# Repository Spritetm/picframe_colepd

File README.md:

### What is this?

This is the firmware, PCB artwork, schematics and case design for a WiFi-enabled color picture frame.

### Contents

- case - OpenSCAD program to build the case. Change the 'render' variable to render the various parts.
- www - PHP and C program running on the server that is used to upload/fetch the pictures.
- firmware - ESP32C3 firmware. Make sure to run menuconfig to point this at your server.
- pcb - Schematics and PCB artwork, in Kicad format.

### More information

[Article on Spritesmods](https://spritesmods.com/?art=wifipicframe)

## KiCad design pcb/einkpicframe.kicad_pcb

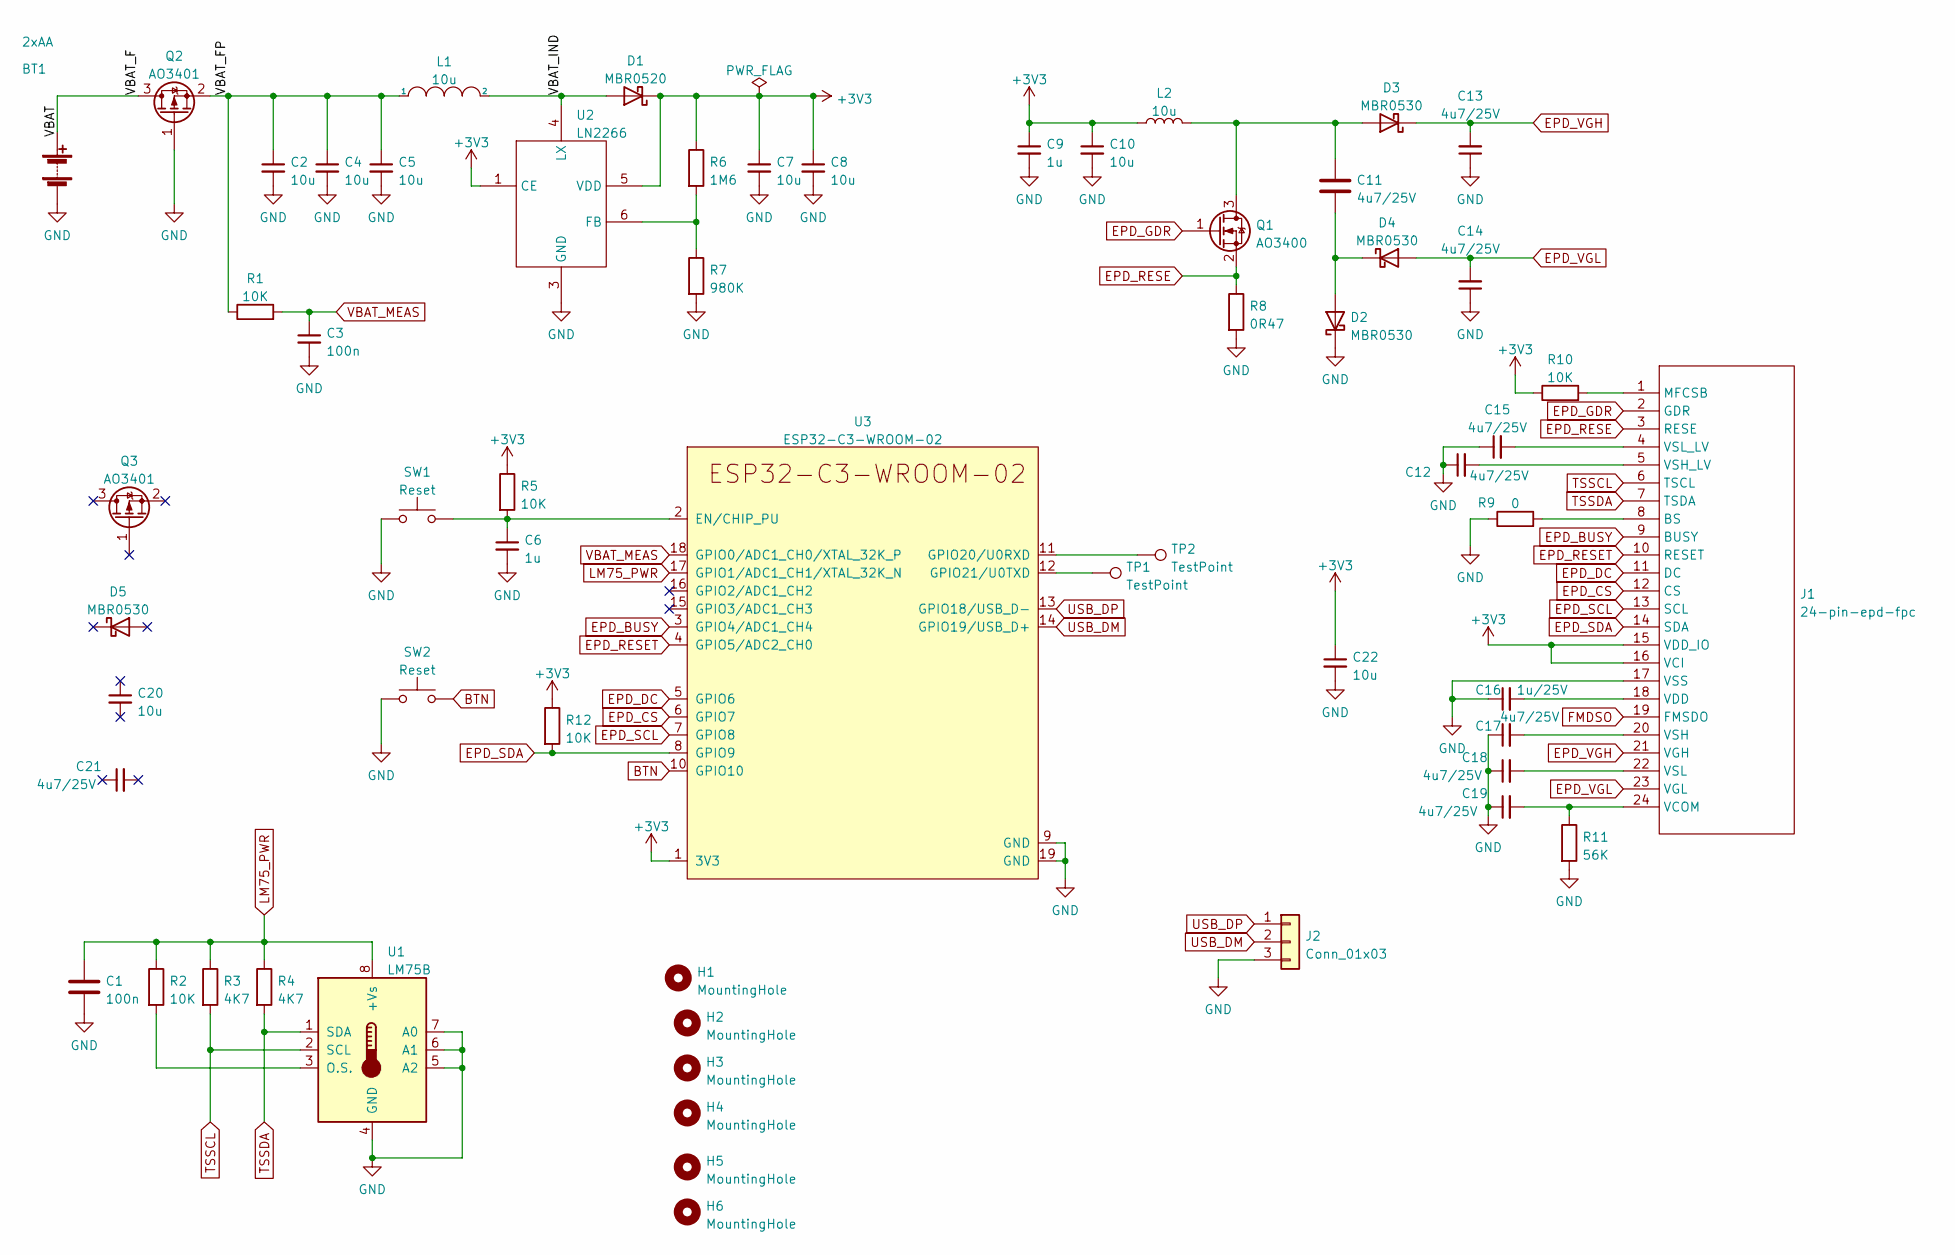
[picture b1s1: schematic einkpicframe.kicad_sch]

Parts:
BT1: 2xAA; 2xaa_pcb_conn
C1, C3: 100n; C_0603_1608Metric
C2, C4, C5, C7, C8, C10, C20, C22: 10u; C_0805_2012Metric
C6, C9: 1u; C_0603_1608Metric
C11, C12, C13, C14, C15, C17, C18, C19, C21: 4u7/25V; C_0603_1608Metric
C16: 1u/25V; C_0603_1608Metric
D1: MBR0520; D_SOD-123
D2, D3, D4, D5: MBR0530; D_SOD-123
H1, H2, H3, H4, H5, H6: MountingHole; MountingHole_3.2mm_M3_ISO14580
J1: 24-pin-epd-fpc; Hirose_FH12-24S-0.5SH_1x24-1MP_P0.50mm_Horizontal_reverse
J2: Conn_01x03; PinHeader_1x03_P2.54mm_Horizontal
L1, L2: 10u; IND_WHC0630
Q1: AO3400; SOT-23
Q2, Q3: AO3401; SOT-23W_Handsoldering
R1, R2, R5, R10, R12: 10K; R_0603_1608Metric
R3, R4: 4K7; R_0603_1608Metric
R6: 1M6; R_0603_1608Metric
R7: 980K; R_0603_1608Metric
R8: 0R47; R_0603_1608Metric
R9: 0; R_0603_1608Metric
R11: 56K; R_0603_1608Metric
SW1, SW2: Reset; SW_SPST_B3S-1000
TP1, TP2: TestPoint; TestPoint_Pad_1.5x1.5mm
U1: LM75B; TSSOP-8_3x3mm_P0.65mm
U2: LN2266; SOT-23-6
U3: ESP32-C3-WROOM-02

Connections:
+3V3: C7.1, C8.1, C9.1, C10.1, C22.1, D1.1 (K), J1.15 (VDD_IO), J1.16 (VCI), L2.1, R5.1, R6.1, R10.1, R12.1, U2.1 (CE), U2.5 (VDD), U3.1 (3V3)
/VBAT: BT1.1 (+), Q2.3 (D)
/VBAT_FP: C2.1, C4.1, C5.1, L1.1, Q2.2 (S), R1.1
/VBAT_IND: D1.2 (A), L1.2, U2.4 (LX)
BTN: SW2.2, U3.10 (GPIO10)
EPD_BUSY: J1.9 (BUSY), U3.3 (GPIO4/ADC1_CH4)
EPD_CS: J1.12 (CS), U3.6 (GPIO7)
EPD_DC: J1.11 (DC), U3.5 (GPIO6)
EPD_GDR: J1.2 (GDR), Q1.1 (G)
EPD_RESE: J1.3 (RESE), Q1.2 (S), R8.1
EPD_RESET: J1.10 (RESET), U3.4 (GPIO5/ADC2_CH0)
EPD_SCL: J1.13 (SCL), U3.7 (GPIO8)
EPD_SDA: J1.14 (SDA), R12.2, U3.8 (GPIO9)
EPD_VGH: C13.2, D3.1 (K), J1.21 (VGH)
EPD_VGL: C14.2, D4.2 (A), J1.23 (VGL)
FMDSO: J1.19 (FMSDO)
GND: BT1.2 (-), C1.2, C2.2, C3.2, C4.2, C5.2, C6.2, C7.2, C8.2, C9.2, C10.2, C12.1, C13.1, C14.1, C15.1, C16.1, C17.1, C18.1, C19.1, C22.2, D2.1 (K), J1.17 (VSS), J2.3, Q2.1 (G), R7.2, R8.2, R9.1, R11.2, SW1.1, SW2.1, U1.4 (GND), U1.5 (A2), U1.6 (A1), U1.7 (A0), U2.3 (GND), U3.9 (GND), U3.19 (GND)
LM75_PWR: C1.1, R2.1, R3.1, R4.1, U1.8 (+Vs), U3.17 (GPIO1/ADC1_CH1/XTAL_32K_N)
unnamed: C11.2, D2.2 (A), D4.1 (K)
unnamed: C11.1, D3.2 (A), L2.2, Q1.3 (D)
unnamed: J1.8 (BS), R9.2
unnamed: J1.1 (MFCSB), R10.2
unnamed: C19.2, J1.24 (VCOM), R11.1
unnamed: C16.2, J1.18 (VDD)
unnamed: C17.2, J1.20 (VSH)
unnamed: C12.2, J1.5 (VSH_LV)
unnamed: C18.2, J1.22 (VSL)
unnamed: C15.2, J1.4 (VSL_LV)
unnamed: R2.2, U1.3 (O.S.)
unnamed: R6.2, R7.1, U2.6 (FB)
unnamed: C6.1, R5.2, SW1.2, U3.2 (EN/CHIP_PU)
unnamed: TP2.1, U3.11 (GPIO20/U0RXD)
unnamed: TP1.1, U3.12 (GPIO21/U0TXD)
TSSCL: J1.6 (TSCL), R3.2, U1.2 (SCL)
TSSDA: J1.7 (TSDA), R4.2, U1.1 (SDA)
USB_DM: J2.2, U3.14 (GPIO19/USB_D+)
USB_DP: J2.1, U3.13 (GPIO18/USB_D-)
VBAT_MEAS: C3.1, R1.2, U3.18 (GPIO0/ADC1_CH0/XTAL_32K_P)

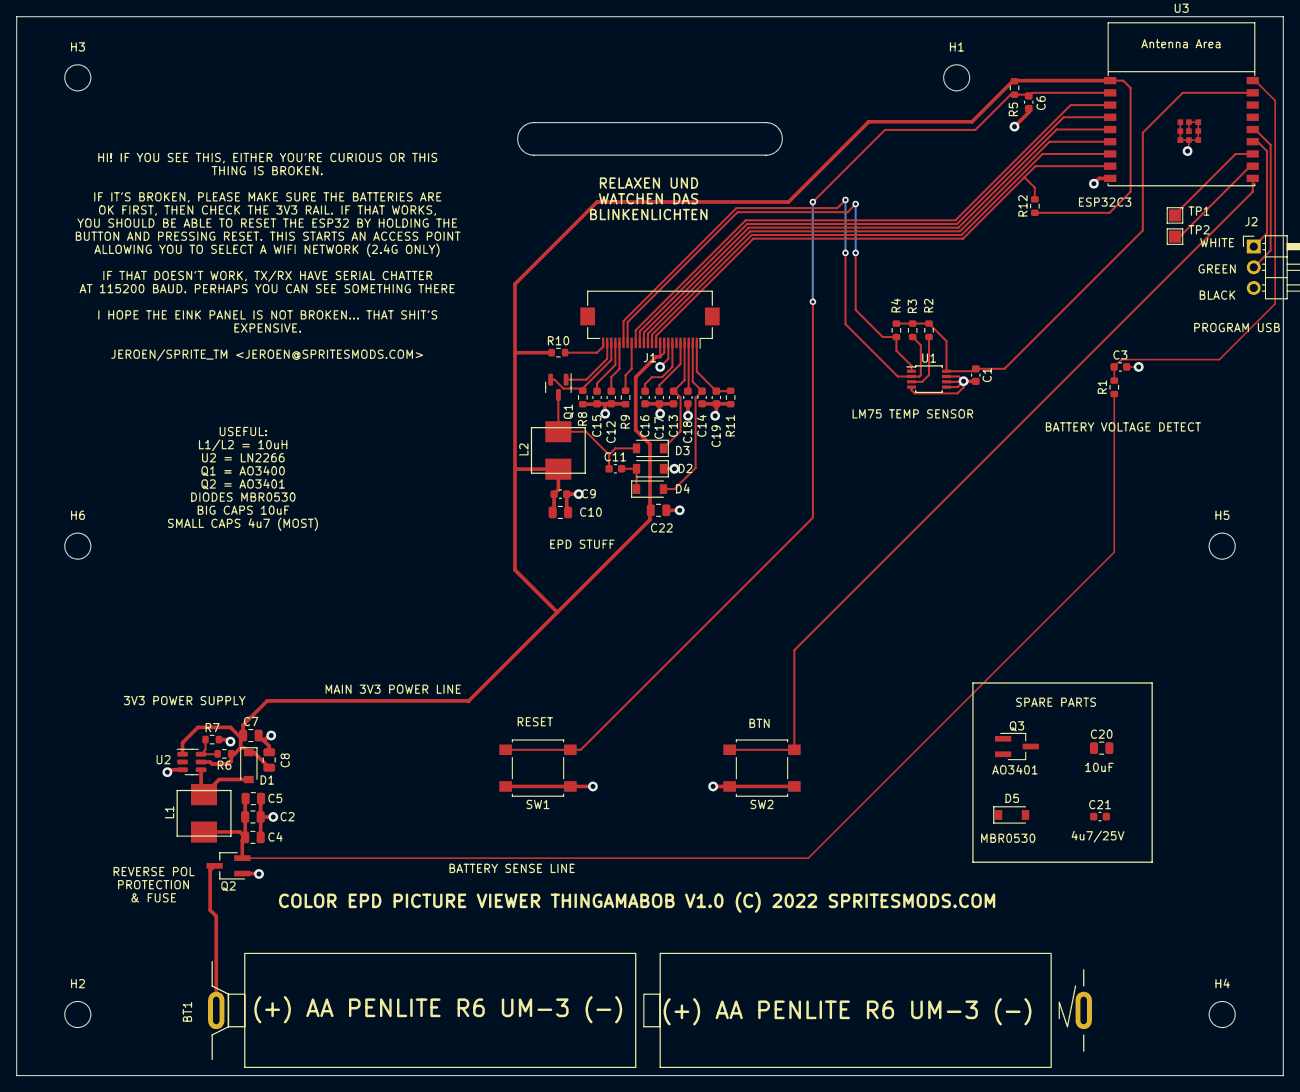
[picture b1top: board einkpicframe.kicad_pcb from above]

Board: 2 copper layers, 155.5 x 130.0 mm, 60 parts (0 on the bottom side), 37 nets.

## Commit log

2022-06-20 Move firmware to firmware dir
2022-06-20 Add web stuff
2022-07-31 Update to pcb
2022-07-31 Add case design
2022-07-31 dependencies
2022-07-31 do not save stl files
2022-07-31 cleanup
2022-07-31 add proper cropper module
2022-07-31 rework uploader
2022-07-31 Fix upload
2022-08-01 Add LAB color mixing code. That was a mistake.
2022-08-01 Fancy up infrastructure
2022-08-01 Clean up firmware
2022-08-01 Switch wifi manager branch
2022-08-02 switch to own branch of wifi-manager
2022-08-02 get firmware down to sub-100uA in sleep
2022-08-02 remove superfluous measurement labels
2022-08-03 Improved sync scheme, make deep sleep work
2022-08-03 Add icon selection, add error handling to sunc, add reacting to button, add battery, add OTA rollback
2022-08-03 Fix that EPD is upside down in frame, add fw rev to database
2022-08-03 Add comments, fix int return vals
2022-08-04 Add database creation stuff
2022-08-04 Use public url for wifi-manager repo
2022-08-04 Optimize conv executable, add how to compile
2022-08-04 hacky fix for ap mode via button, make base url configurable in menuconfig
2022-08-07 Improve colors
2022-08-24 abort before inserting into db on conv error
2022-08-24 Rework to esp-idf 5.0 apis
2022-08-24 Improve low battery handling, add guard for re-downloading rolled-back OTA
2022-10-13 add wifimanager fixes
2022-10-13 Add beerware license
2023-04-23 Squash all commits in order to remove personal information. Sorry, you don't get to see the history on this project...
2023-04-23 Fix readme

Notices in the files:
pcb/einkpicframe.kicad_pcb:
COLOR EPD PICTURE VIEWER THINGAMABOB V1.0 (C) 2022 SPRITESMODS.COM
